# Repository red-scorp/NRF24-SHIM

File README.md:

# NRF24-SHIM project

NRF24-SHIM (mini-HAT), an interface board for NRF32L01+ radio boards for Raspberry Pi.

This project came to reality when I was looking for a way to connect standard NRF24L01+ module to my Pi.
I had found many tutorials explaining how to connect NRF24 modules to Pi but no ready made board or even proper schematics.
"Hmm... DIY!" I've told myself and here we are.

## NRF24-SHIM

Raspberry Pi 40-pin **NRF24-SHIM** mini-HAT.

Preview:

[Schematics in PDF format](doc/NRF24-SHIM.pdf)

Features:

- locked Pi headers
- locked NRF24 headers
- double set of Pi headers (for inside and outside mount)
- SPI0/SPI1 bus selection
- CE/IRQ selection
- can be used as SHIM (no headers) or HAT (with headers)

Pins Configuration:

|NRF24 Pin |Option 1 |Option 2 |
|----------|---------|---------|
|CE        |GPIO22\* |GPIO25   |
|CSN       |GPIO8\*  |GPIO18   |
|SCK       |GPIO11\* |GPIO21   |
|MOSI      |GPIO10\* |GPIO20   |
|MISO      |GPIO9\*  |GPIO19   |
|IRQ       |GPIO23   |GPIO24   |

\*) the pin is connected by default.

CAM files are available.

## NRF24-mini-SHIM

Raspberry Pi **NTF32-mini-SHIM** micro-HAT.

Preview:

[Schematics in PDF format](doc/NRF24-mini-SHIM.pdf)

Features:

- locked Pi headers
- locked NRF24 headers
- CE/IRQ selection
- very small size
- fits on 26- and 40-pin Pi headers

Pins Configuration:

|NRF24 Pin |Option 1 |Option 2 |
|----------|---------|---------|
|CE        |GPIO22\* |GPIO25   |
|CSN       |GPIO8\*  |         |
|SCK       |GPIO11\* |         |
|MOSI      |GPIO10\* |         |
|MISO      |GPIO9\*  |         |
|IRQ       |GPIO23   |GPIO24   |

\*) the pin is connected by default.

CAM files are available.

## NRF24-zero-SHIM

Raspberry Pi zero 40-pin **NRF24-zero-SHIM** mini-HAT.

Preview:

[Schematics in PDF format](doc/NRF24-zero-SHIM.pdf)

Features:

- locked Pi headers
- locked NRF24 headers
- Pi zero board style
- SPI0/SPI1 bus selection
- CE/IRQ selection
- double NRF24 configuration possible
- can be used as SHIM (no headers) or HAT (with headers)

Pins Configuration:

|NRF24 Pin |Option 1 |Option 2 |Option 3 |Option 4 |Option 5 |
|----------|---------|---------|---------|---------|---------|
|P0 CE     |GPIO22\* |GPIO25   |GPIO27   |         |         |
|P0 CSN    |GPIO8\*  |GPIO7    |GPIO18   |GPIO17   |GPIO16   |
|P0 SCK    |GPIO11\* |GPIO21   |         |         |         |
|P0 MOSI   |GPIO10\* |GPIO20   |         |         |         |
|P0 MISO   |GPIO9\*  |GPIO19   |         |         |         |
|P0 IRQ    |GPIO23   |GPIO24   |         |         |         |
|P1 CE     |GPIO22   |GPIO25\* |GPIO27   |         |         |
|P1 CSN    |GPIO8    |GPIO7    |GPIO18\* |GPIO17   |GPIO16   |
|P1 SCK    |GPIO11   |GPIO21\* |         |         |         |
|P1 MOSI   |GPIO10   |GPIO20\* |         |         |         |
|P1 MISO   |GPIO9    |GPIO19\* |         |         |         |
|P1 IRQ    |GPIO23   |GPIO24   |         |         |         |

\*) the pin is connected by default.

CAM files are available.

## BOM

Bill Of Materials is currently available only for LCSC Electronic Components Distributor, which is probably cheapest anyway.

### LCSC BOM

|Designator                      |Part/Value |Package/Footprint |LCSC # |
|--------------------------------|-----------|------------------|-------|
|C1, C3\*                        |Cap. 100nF |0402              |C1525  |
|C2, C4\*                        |Cap. 1uF   |0603              |C15849 |
|R1, R2, R3, R4, R5, R6, R7, R8\*|Res. 10K   |0402              |C25744 |

\*) These passive components are optional but it's recommended to install them.

## Links

- [pinout.xyz](https://pinout.xyz/) - a brilliant resource on topic of Pi's pinout and HATs.
- [raspberrypi/hats](https://github.com/raspberrypi/hats) - Pi's HAT specification.
- [Communication between Arduino AND Raspberry Pi using NRF24L01](https://medium.com/@anujdev11/communication-between-arduino-and-raspberry-pi-using-nrf24l01-818687f7f363) - how to setup NRF24L01 with Pi.
- [Funkkommunikation zwischen Raspberry Pi’s und Arduinos (2.4 GHz)](https://tutorials-raspberrypi.de/funkkommunikation-zwischen-raspberry-pis-und-arduinos-2-4-ghz/) - how to setup NRF24L01 with Pi in German.
- [Connecting an nRF24L01+ to Raspberry Pi](https://www.hackster.io/wirekraken/connecting-an-nrf24l01-to-raspberry-pi-9c0a57) - one more setup example.

## How to help

Your contributions as code, resources, or finances are welcome! Please contact me directly via email at andriy.golovnya@gmail.com or through my [GitHub profile](https://github.com/red-scorp).

If you'd like to make a financial contribution, you can donate via [PayPal](http://paypal.me/redscorp) or [Ko-Fi](http://ko-fi.com/redscorp). Your support is greatly appreciated.

Thanks in advance!

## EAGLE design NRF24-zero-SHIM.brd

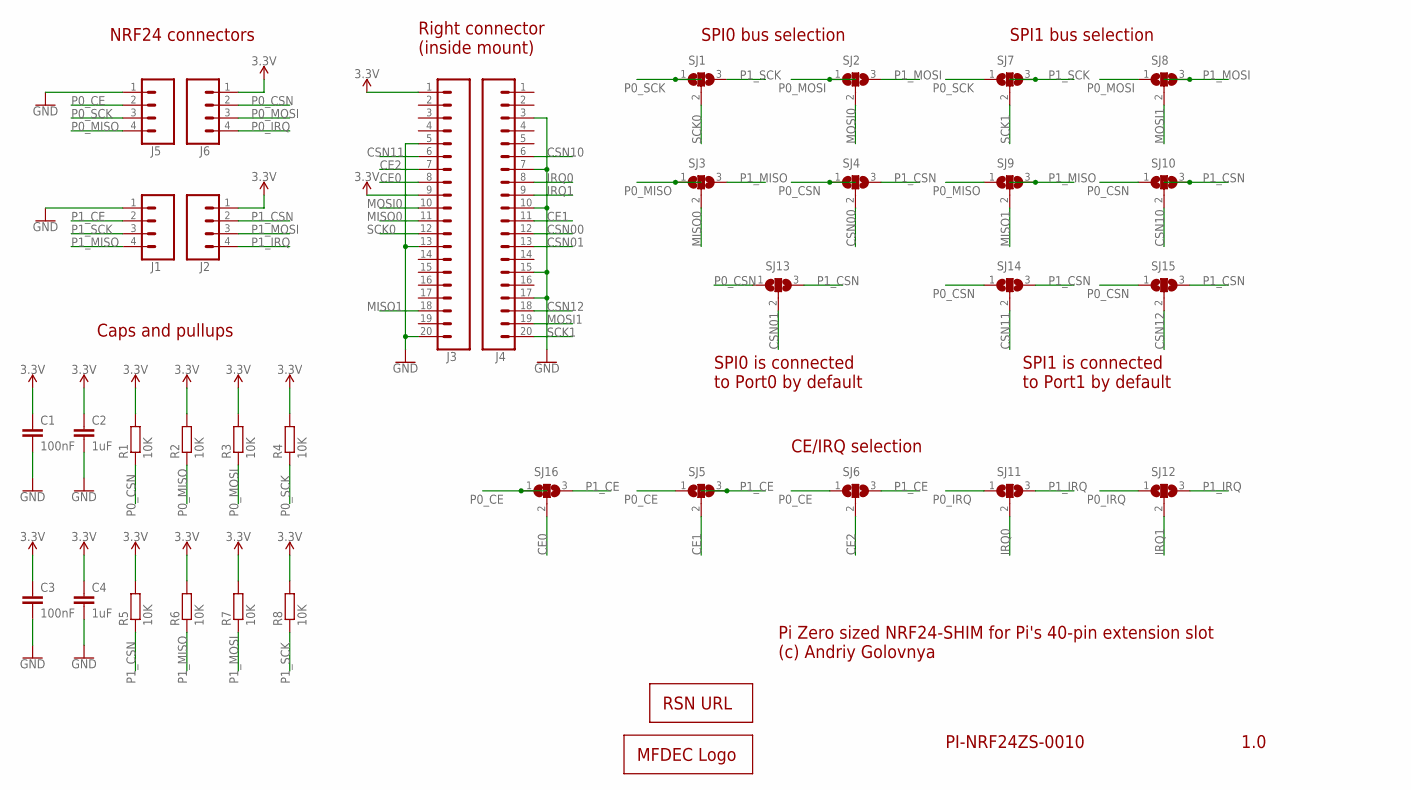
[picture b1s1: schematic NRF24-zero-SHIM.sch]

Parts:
C1, C3: 100nF; C0402
C2, C4: 1uF; C0603
J1, J2, J5, J6: CONN_04LOCK; 1X04_LOCK
J3, J4: CONN_20LOCK; 1X20_LOCK
LOGO1: MFDECLOGO_SQ_8MM; MFDEC_SQ_8MM
LOGO3: RSNURL_QR_10MM
R1, R2, R3, R4, R5, R6, R7, R8: 10K; R0402
SJ1, SJ2, SJ3, SJ4, SJ5, SJ6, SJ7, SJ8, SJ9, SJ10, SJ11, SJ12, SJ13, SJ14, SJ15, SJ16: SJ2; SJ_2

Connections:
3.3V: C1.1, C2.1, C3.1, C4.1, J2.1, J3.1, J3.9, J6.1, R1.2, R2.2, R3.2, R4.2, R5.2, R6.2, R7.2, R8.2
CE0: J3.8, SJ16.2
CE1: J4.11, SJ5.2
CE2: J3.7, SJ6.2
CSN00: J4.12, SJ4.2
CSN01: J4.13, SJ13.2
CSN10: J4.6, SJ10.2
CSN11: J3.6, SJ14.2
CSN12: J4.18, SJ15.2
GND: C1.2, C2.2, C3.2, C4.2, J1.1, J3.5, J3.13, J3.20, J4.3, J4.7, J4.10, J4.15, J4.17, J5.1
IRQ0: J4.8, SJ11.2
IRQ1: J4.9, SJ12.2
MISO0: J3.11, SJ3.2
MISO1: J3.18, SJ9.2
MOSI0: J3.10, SJ2.2
MOSI1: J4.19, SJ8.2
P0_CE: J5.2, SJ5.1, SJ6.1, SJ16.1
P0_CSN: J6.2, R1.1, SJ4.1, SJ10.1, SJ13.1, SJ14.1, SJ15.1
P0_IRQ: J6.4, SJ11.1, SJ12.1
P0_MISO: J5.4, R2.1, SJ3.1, SJ9.1
P0_MOSI: J6.3, R3.1, SJ2.1, SJ8.1
P0_SCK: J5.3, R4.1, SJ1.1, SJ7.1
P1_CE: J1.2, SJ5.3, SJ6.3, SJ16.3
P1_CSN: J2.2, R5.1, SJ4.3, SJ10.3, SJ13.3, SJ14.3, SJ15.3
P1_IRQ: J2.4, SJ11.3, SJ12.3
P1_MISO: J1.4, R6.1, SJ3.3, SJ9.3
P1_MOSI: J2.3, R7.1, SJ2.3, SJ8.3
P1_SCK: J1.3, R8.1, SJ1.3, SJ7.3
SCK0: J3.12, SJ1.2
SCK1: J4.20, SJ7.2

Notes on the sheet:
1.0
PI-NRF24ZS-0010
Pi Zero sized NRF24-SHIM for Pi's 40-pin extension slot (c) Andriy Golovnya
NRF24 connectors
Caps and pullups
Right connector (inside mount)
SPI0 bus selection
SPI0 is connected to Port0 by default
CE/IRQ selection
SPI1 bus selection
SPI1 is connected to Port1 by default

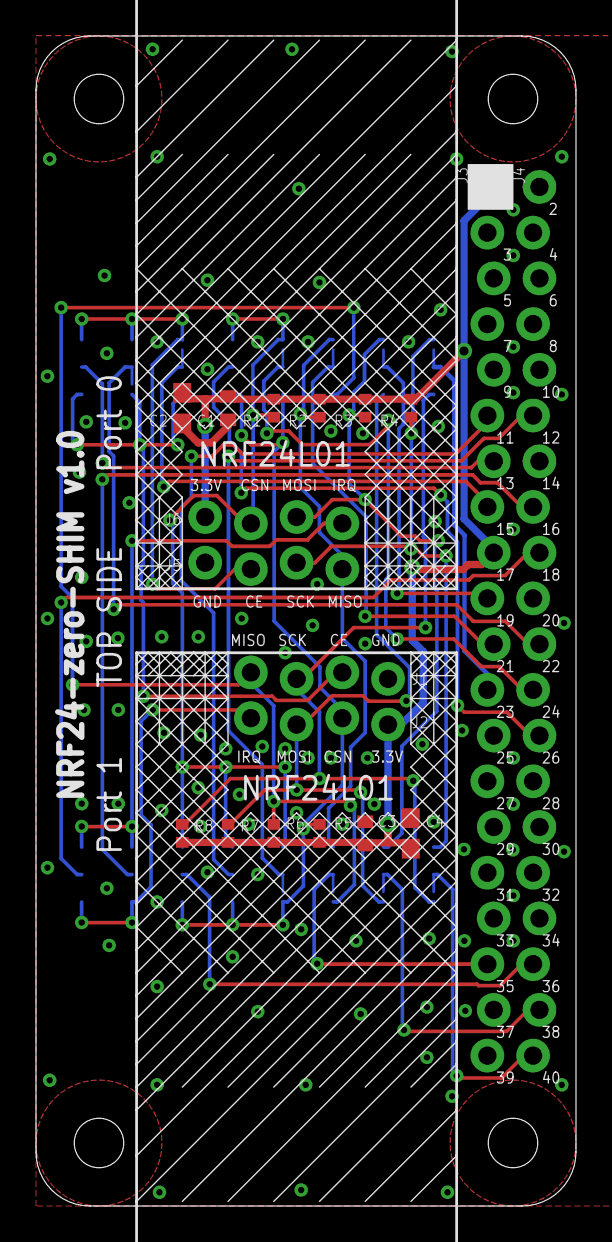
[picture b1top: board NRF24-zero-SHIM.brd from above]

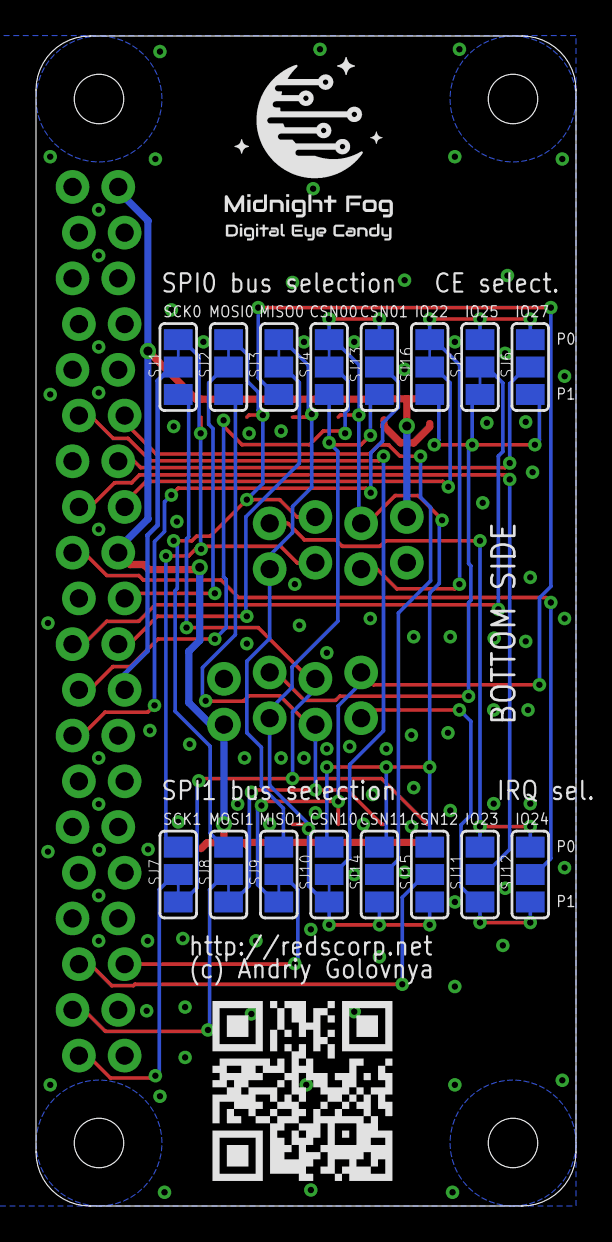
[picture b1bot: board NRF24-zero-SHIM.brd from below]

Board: 2 copper layers, 30.0 x 65.0 mm, 36 parts (18 on the bottom side), 30 nets.

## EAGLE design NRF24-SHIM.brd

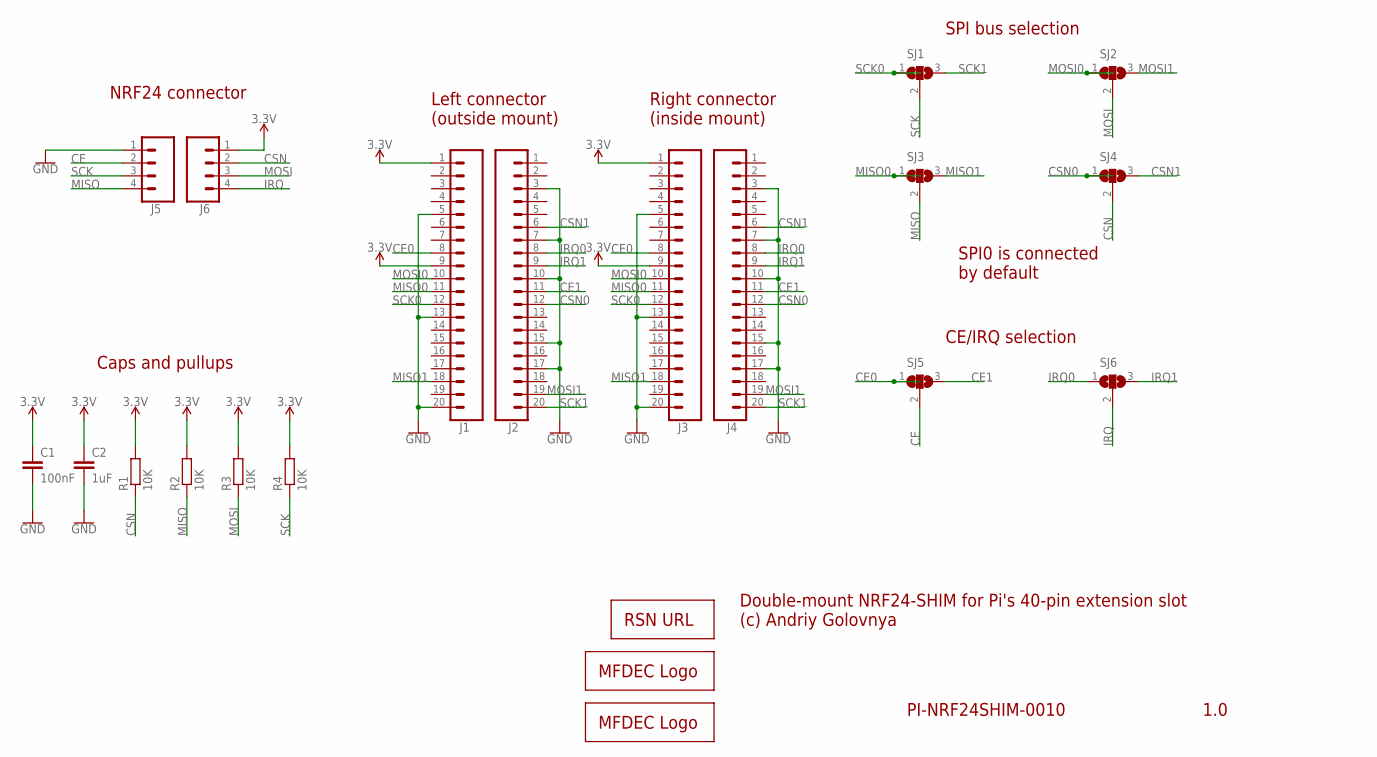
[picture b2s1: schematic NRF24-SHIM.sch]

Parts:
C1: 100nF; C0402
C2: 1uF; C0603
J1, J2, J3, J4: CONN_20LOCK; 1X20_LOCK
J5, J6: CONN_04LOCK; 1X04_LOCK
LOGO1: MFDECLOGO_SQ_8MM; MFDEC_SQ_8MM
LOGO2: MFDECLOGO_L_20MM; MFDEC_L_20MM
LOGO3: RSNURL_QR_10MM
R1, R2, R3, R4: 10K; R0402
SJ1, SJ2, SJ3, SJ4, SJ5, SJ6: SJ2; SJ_2

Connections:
3.3V: C1.1, C2.1, J1.1, J1.9, J3.1, J3.9, J6.1, R1.2, R2.2, R3.2, R4.2
CE: J5.2, SJ5.2
CE0: J1.8, J3.8, SJ5.1
CE1: J2.11, J4.11, SJ5.3
CSN: J6.2, R1.1, SJ4.2
CSN0: J2.12, J4.12, SJ4.1
CSN1: J2.6, J4.6, SJ4.3
GND: C1.2, C2.2, J1.5, J1.13, J1.20, J2.3, J2.7, J2.10, J2.15, J2.17, J3.5, J3.13, J3.20, J4.3, J4.7, J4.10, J4.15, J4.17, J5.1
IRQ: J6.4, SJ6.2
IRQ0: J2.8, J4.8, SJ6.1
IRQ1: J2.9, J4.9, SJ6.3
MISO: J5.4, R2.1, SJ3.2
MISO0: J1.11, J3.11, SJ3.1
MISO1: J1.18, J3.18, SJ3.3
MOSI: J6.3, R3.1, SJ2.2
MOSI0: J1.10, J3.10, SJ2.1
MOSI1: J2.19, J4.19, SJ2.3
SCK: J5.3, R4.1, SJ1.2
SCK0: J1.12, J3.12, SJ1.1
SCK1: J2.20, J4.20, SJ1.3

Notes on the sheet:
1.0
PI-NRF24SHIM-0010
Double-mount NRF24-SHIM for Pi's 40-pin extension slot (c) Andriy Golovnya
NRF24 connector
Caps and pullups
Left connector (outside mount)
Right connector (inside mount)
SPI bus selection
SPI0 is connected by default
CE/IRQ selection

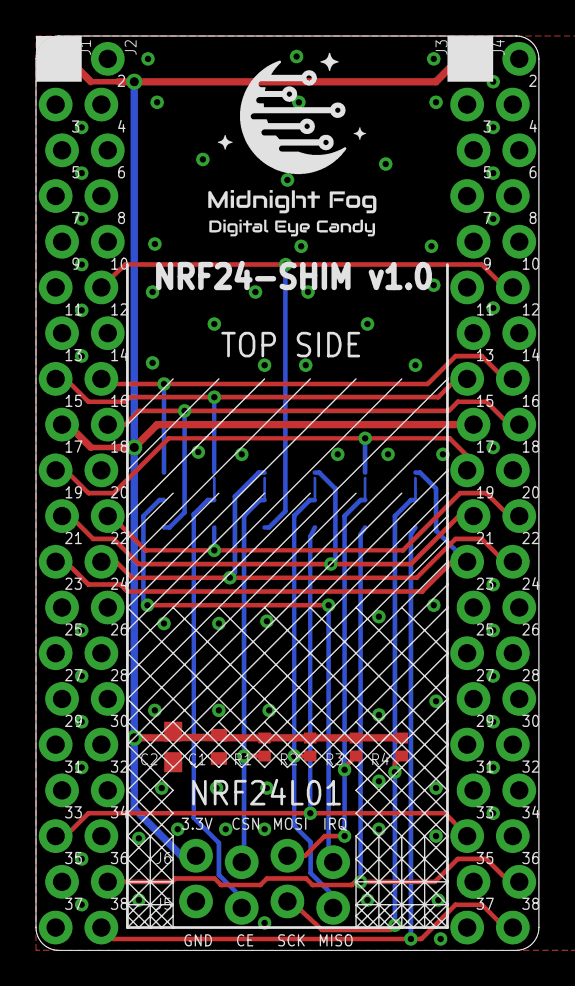
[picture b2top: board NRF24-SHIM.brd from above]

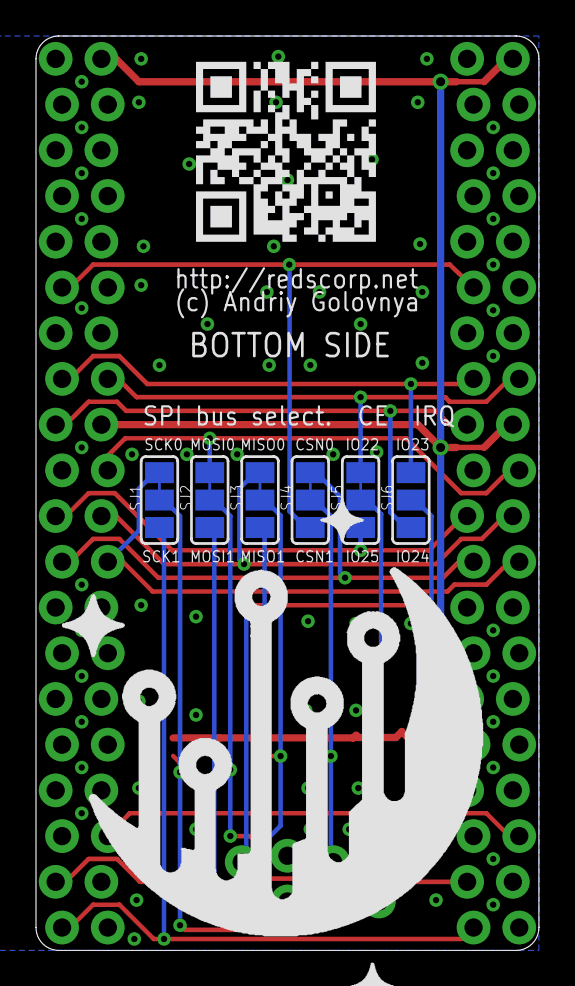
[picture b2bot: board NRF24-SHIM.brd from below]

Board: 2 copper layers, 27.9 x 50.8 mm, 21 parts (8 on the bottom side), 20 nets.

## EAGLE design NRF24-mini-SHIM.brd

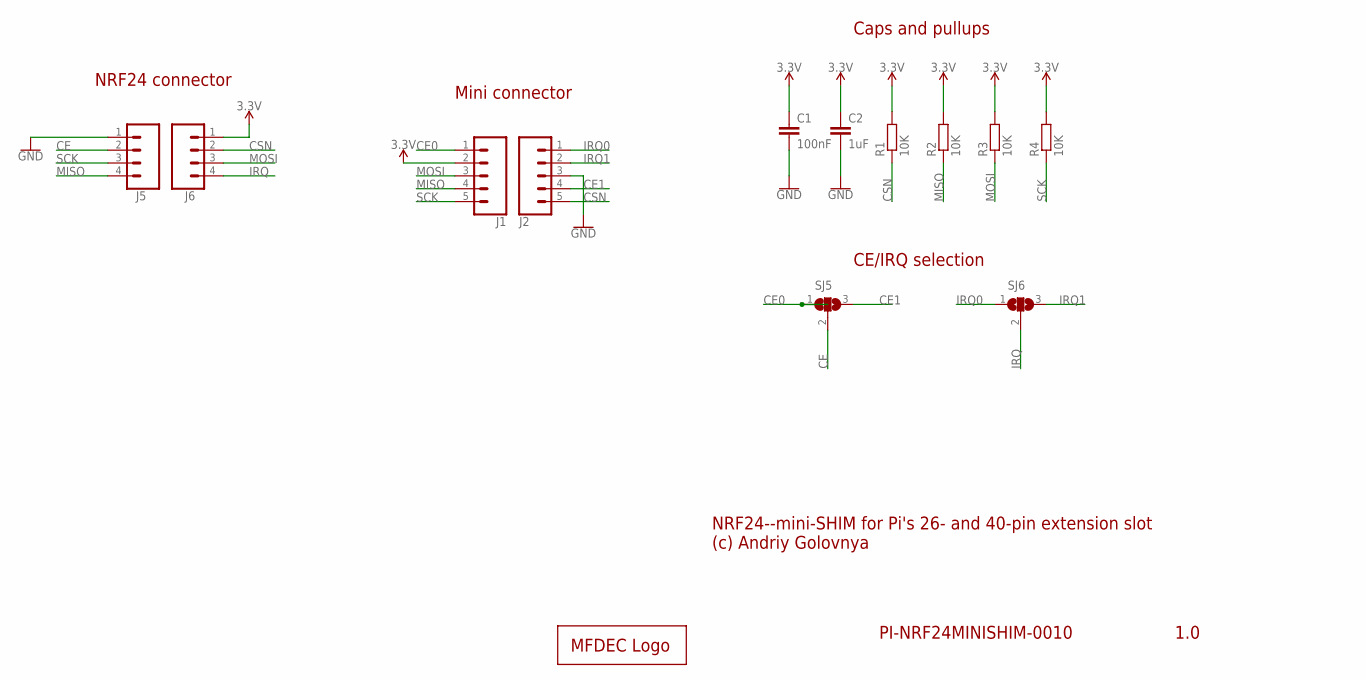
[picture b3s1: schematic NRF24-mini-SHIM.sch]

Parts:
C1: 100nF; C0402
C2: 1uF; C0603
J1, J2: CONN_05LOCK; 1X05_LOCK
J5, J6: CONN_04LOCK; 1X04_LOCK
LOGO1: MFDECLOGO_L_10MM; MFDEC_L_10MM
R1, R2, R3, R4: 10K; R0402
SJ5, SJ6: SJ2; SJ_2

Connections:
3.3V: C1.1, C2.1, J1.2, J6.1, R1.2, R2.2, R3.2, R4.2
CE: J5.2, SJ5.2
CE0: J1.1, SJ5.1
CE1: J2.4, SJ5.3
CSN: J2.5, J6.2, R1.1
GND: C1.2, C2.2, J2.3, J5.1
IRQ: J6.4, SJ6.2
IRQ0: J2.1, SJ6.1
IRQ1: J2.2, SJ6.3
MISO: J1.4, J5.4, R2.1
MOSI: J1.3, J6.3, R3.1
SCK: J1.5, J5.3, R4.1

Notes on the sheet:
1.0
PI-NRF24MINISHIM-0010
NRF24--mini-SHIM for Pi's 26- and 40-pin extension slot (c) Andriy Golovnya
NRF24 connector
Caps and pullups
Mini connector
CE/IRQ selection

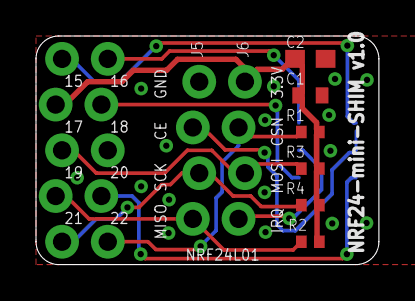
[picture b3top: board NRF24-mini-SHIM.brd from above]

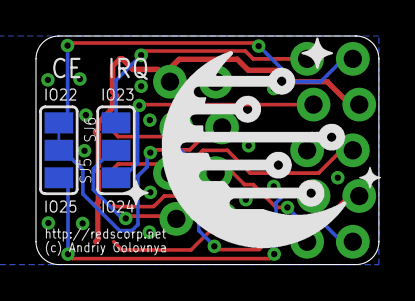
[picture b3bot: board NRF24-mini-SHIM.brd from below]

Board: 2 copper layers, 19.1 x 12.7 mm, 13 parts (3 on the bottom side), 12 nets.

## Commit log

2020-12-07 Initial board design
2020-12-07 removed some unneeded stuff from the board.
2020-12-08 Add more pullups. Add more solder joints. Did some tracing.
2020-12-09 Changed NRF24 connector to locked one. Moved passive components closer to the NRF24 connector. Add descriptive texts. Moved some stuff around.
2020-12-09 Generated CAM.
2020-12-10 Moved some traces around. Added some NRF24 location decoration.
2020-12-10 Generated new CAM.
2020-12-11 Moved some traces around. Fixed schematics description.
2020-12-11 Add basic readme file
2020-12-11 Add schematics in PDF format.
2020-12-13 Use more locking pin headers. Moved some traces.
2020-12-14 Made minor adjustments to traces and vias.
2020-12-14 Add NRF24-mini-SHIM board design.
2020-12-14 Generated schematics in PDF.
2020-12-14 Updated README.
2020-12-18 Generated new PNG board preview.
2020-12-19 Minor changes in README.
2020-12-22 Minor fix in traces path
2020-12-23 Initial prototype of NRF24-zero-SHIM.
2020-12-23 Changed the way how solder joins are organized.
2020-12-24 Added zero-sized board.
2020-12-24 Generated PNG preview image.
2020-12-25 Updated description.
2021-01-04 Moved some traces and vias to allow better ground surface. Generated new PNG preview. Generated new CAM.
2021-01-04 Add Port 0 and Port 1 texts. Moved some texts around. Generated new PNG preview. Generated new CAM.
2021-01-04 Added some links to README.
2021-01-05 Simplified document names. Generated PDF schematics.
2021-01-10 Fixed document description.
2021-01-10 Added link to raspberrypi/hats
2021-01-13 Fixed description
2021-03-01 Fix readme.
2021-07-29 Make round cutouts in screwing area. Generated CAM files. Generated PNG previews.
2021-12-05 cleanup.
2022-01-24 Added Ko-Fi link
2022-02-06 Updated descriptions
2023-08-28 Updated 'How to help' section.

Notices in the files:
parts and their libraries:
SparkFun-PowerSymbols: Licensing: Creative Commons ShareAlike 4.0 International - https://creativecommons.org/licenses/by-sa/4.0
